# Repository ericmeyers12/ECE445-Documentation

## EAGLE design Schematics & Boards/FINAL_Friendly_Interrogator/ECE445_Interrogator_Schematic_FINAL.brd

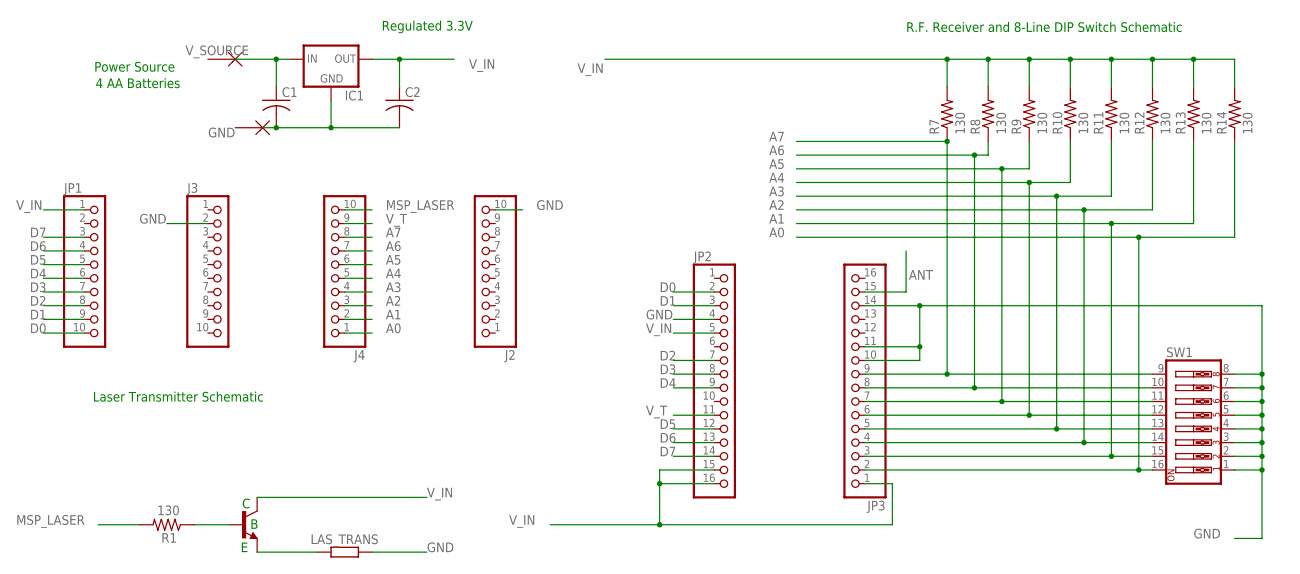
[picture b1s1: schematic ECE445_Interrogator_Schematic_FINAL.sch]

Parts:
C1, C2: C-US050-025X075; C050-025X075
IC1: 78LXX
J2, J3, J4: PINHD-1X10; 1X10
JP1: PINHD-1X10; 1X10
JP2, JP3: PINHD-1X16; 1X16
LAS_TRANS: R-EU_0204/5; 0204/5
Q2: BC338; TO92-EBC
R1, R7, R8, R9, R10, R11, R12, R13, R14: 130; 0204/5
SW1: SW_DIP-8; EDG-08
U$1, U$2: NO_CONNECT

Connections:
A0: J4.1, JP3.2, R14.1, SW1.16
A1: J4.2, JP3.3, R13.1, SW1.15
A2: J4.3, JP3.4, R12.1, SW1.14
A3: J4.4, JP3.5, R11.1, SW1.13
A4: J4.5, JP3.6, R10.1, SW1.12
A5: J4.6, JP3.7, R9.1, SW1.11
A6: J4.7, JP3.8, R8.1, SW1.10
A7: J4.8, JP3.9, R7.1, SW1.9
ANT: JP3.15
D0: JP1.10, JP2.2
D1: JP1.9, JP2.3
D2: JP1.8, JP2.7
D3: JP1.7, JP2.8
D4: JP1.6, JP2.9
D5: JP1.5, JP2.12
D6: JP1.4, JP2.13
D7: JP1.3, JP2.14
GND: C1.2, C2.2, IC1.GND, J2.10, J3.2, JP2.4, JP3.10, JP3.11, JP3.14, LAS_TRANS.2, SW1.1, SW1.2, SW1.3, SW1.4, SW1.5, SW1.6, SW1.7, SW1.8, U$1.P$1
MSP_LASER: J4.10, R1.2
unnamed: LAS_TRANS.1, Q2.E
unnamed: Q2.B, R1.1
V_IN: C2.1, IC1.OUT, JP1.1, JP2.5, JP2.15, JP2.16, JP3.1, Q2.C, R7.2, R8.2, R9.2, R10.2, R11.2, R12.2, R13.2, R14.2
V_SOURCE: C1.1, IC1.IN, U$2.P$1
V_T: J4.9, JP2.11

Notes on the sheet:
Power Source
4 AA Batteries
R.F. Receiver and 8-Line DIP Switch Schematic
Laser Transmitter Schematic
Regulated 3.3V

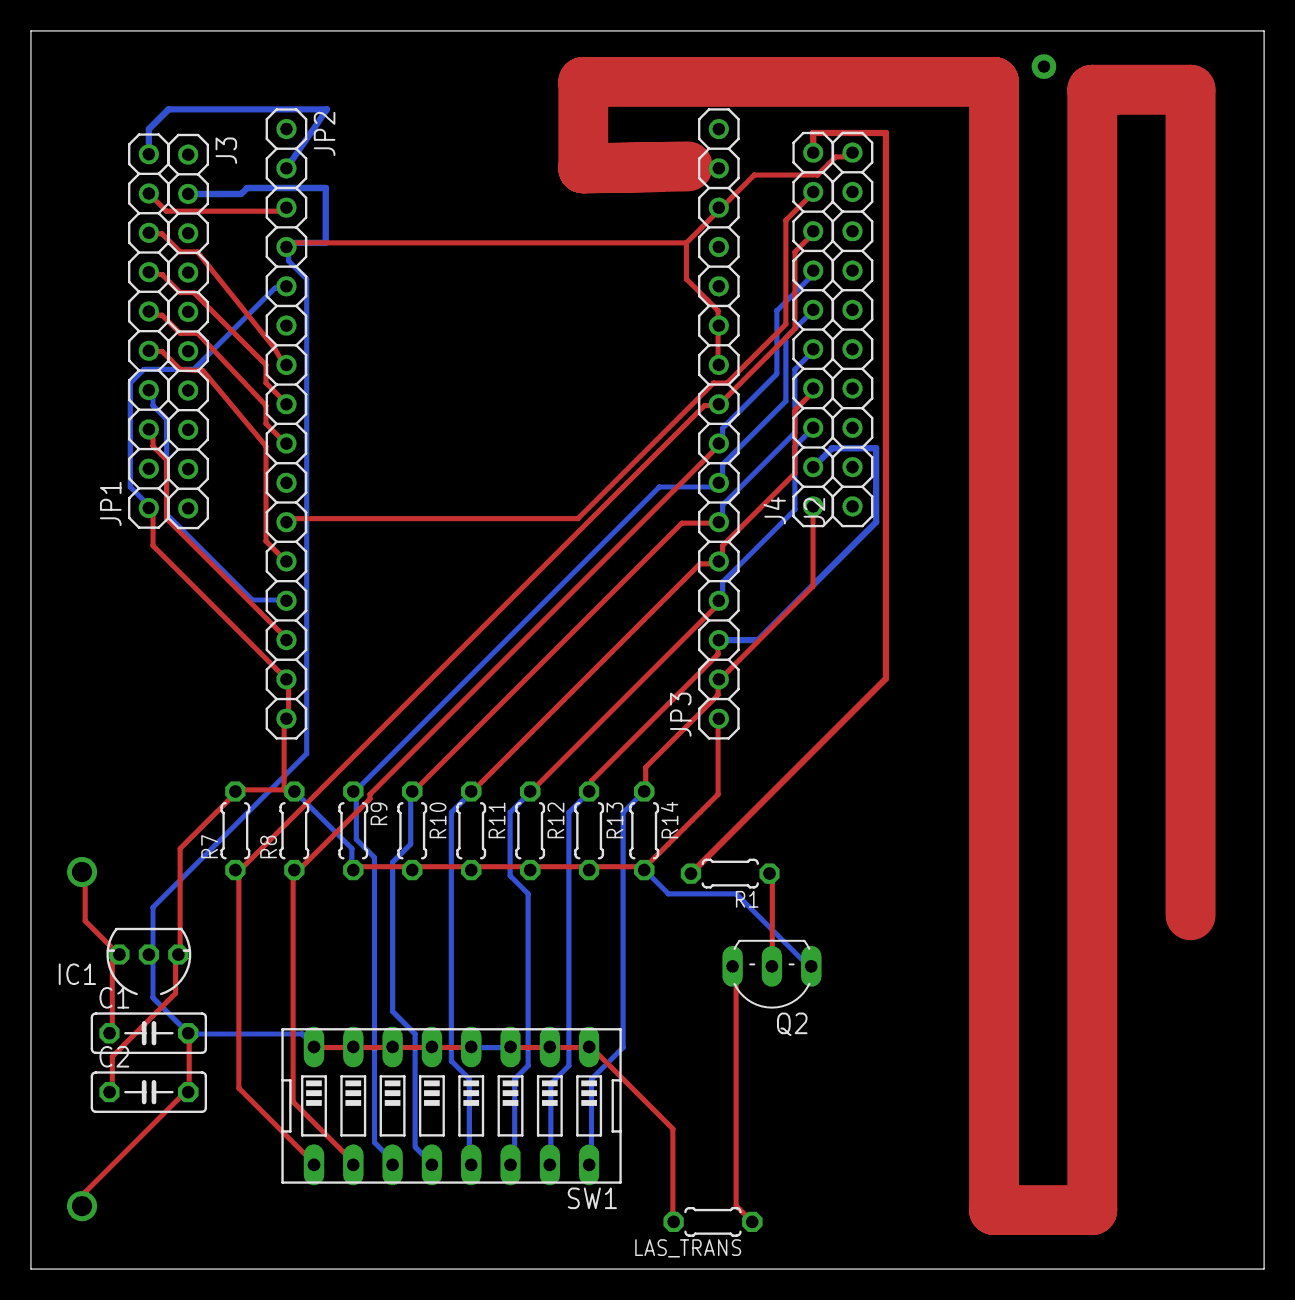
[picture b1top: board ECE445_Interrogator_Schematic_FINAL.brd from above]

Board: 2 copper layers, 79.7 x 80.0 mm, 23 parts (0 on the bottom side), 23 nets.

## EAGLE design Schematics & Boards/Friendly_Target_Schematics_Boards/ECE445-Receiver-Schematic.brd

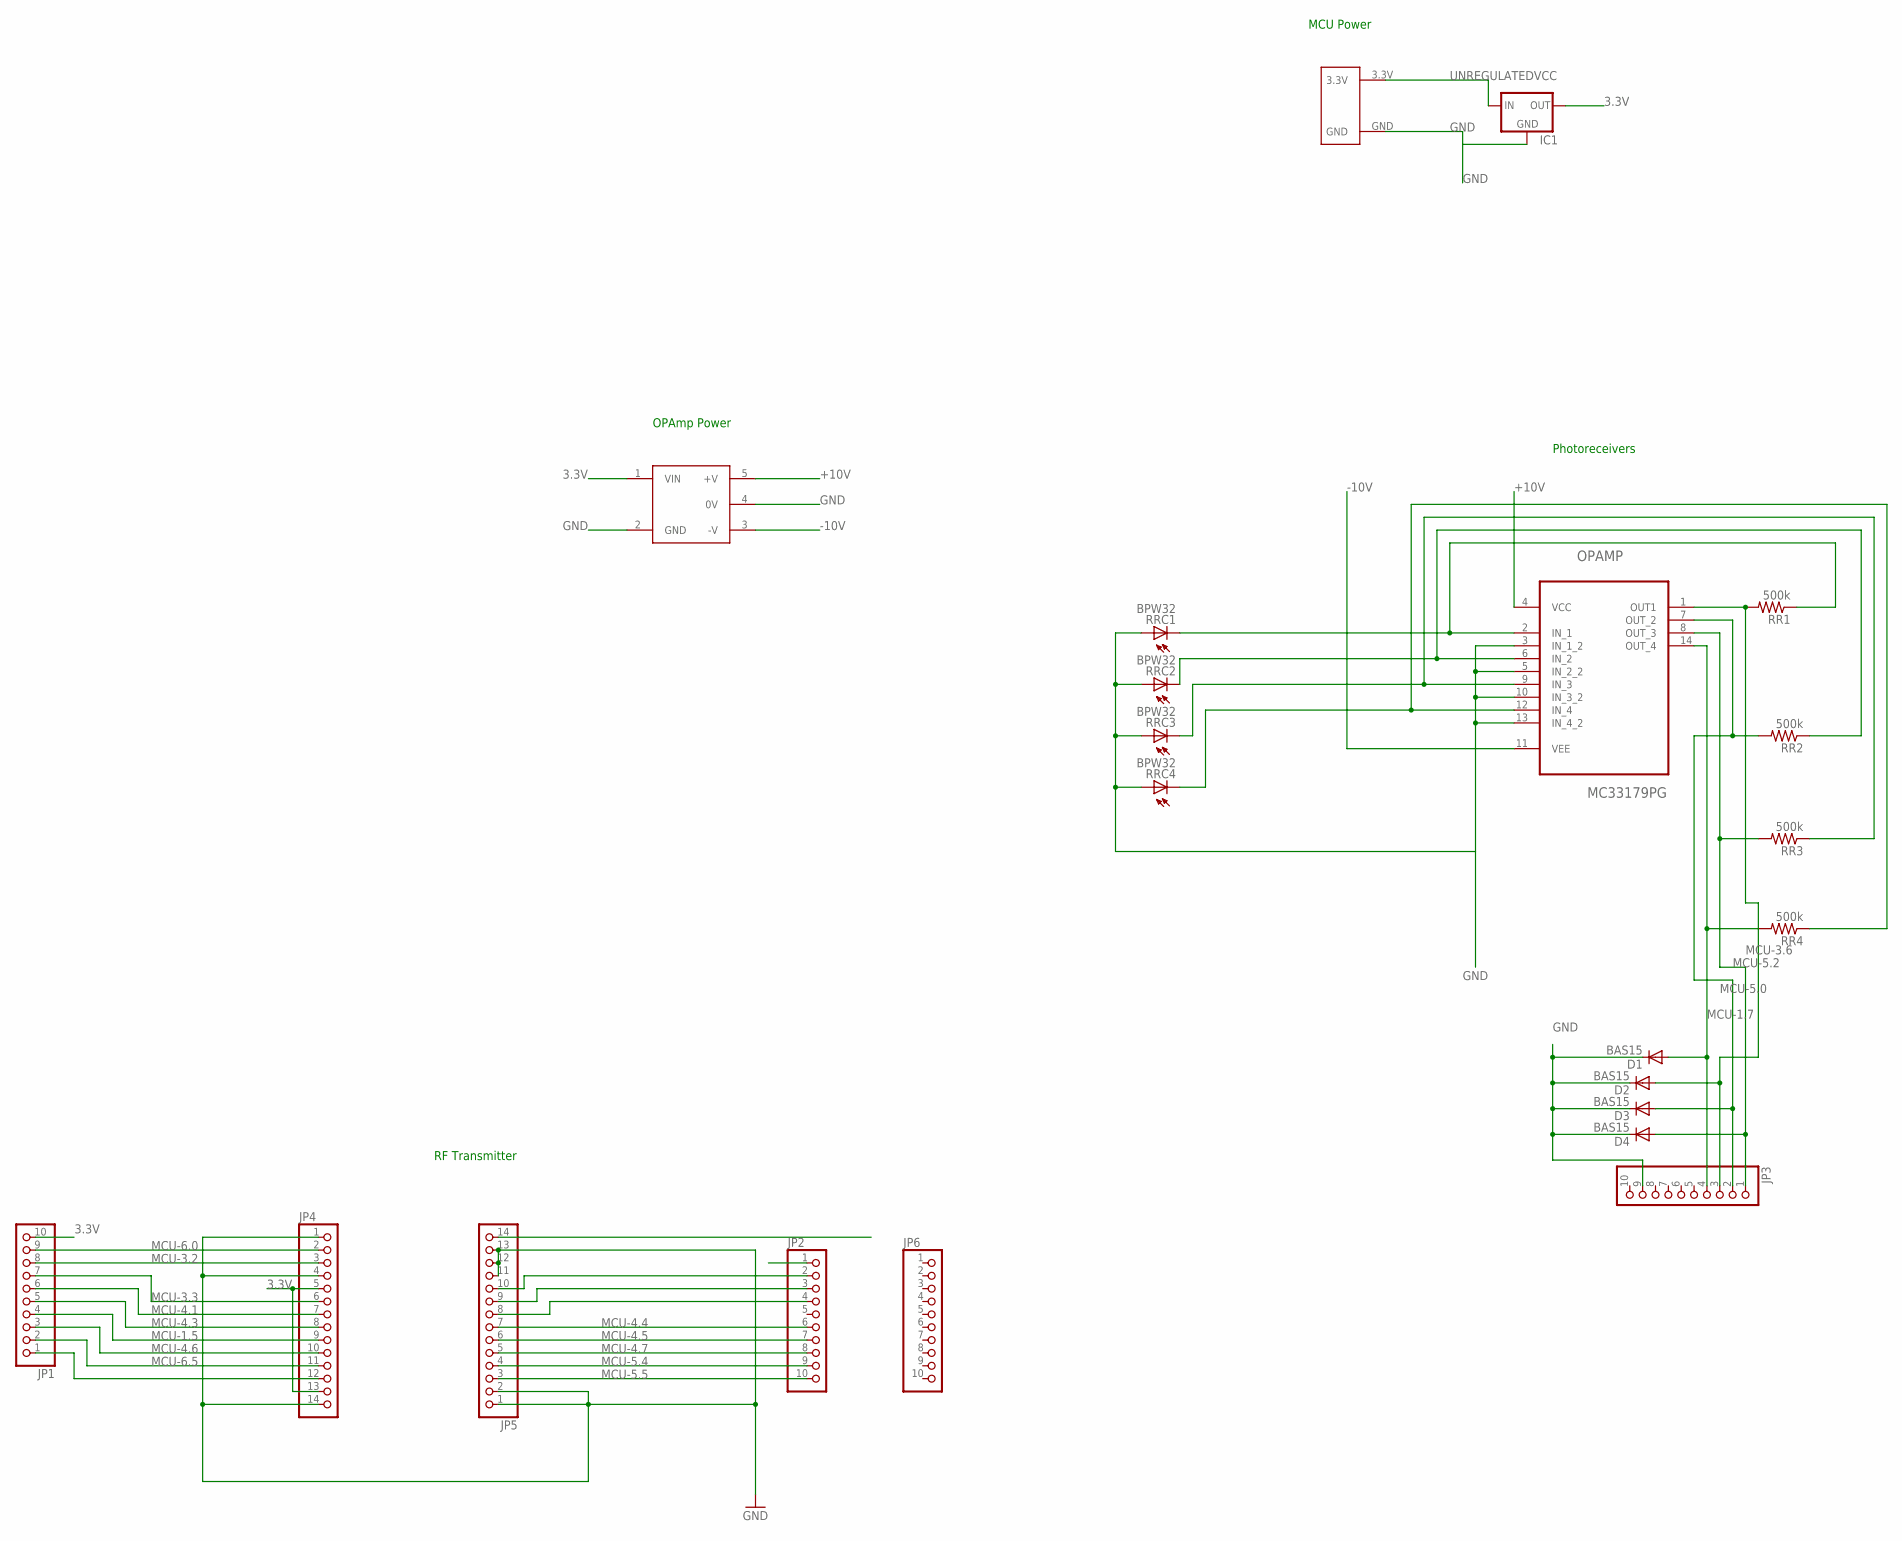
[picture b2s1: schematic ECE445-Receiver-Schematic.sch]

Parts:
D1, D2, D3, D4: BAS15; DO34-7
IC1: 78LXX
JP1, JP2, JP3, JP6: PINHD-1X10; 1X10
JP4, JP5: PINHD-1X14; 1X14
OPAMP: MC33179PG; DIP254P762X469-14
RR1, RR2, RR3, RR4: 500k; 0204/5
RRC1, RRC2, RRC3, RRC4: BPW32
U$13: PDM1-S3-D12-S
U$14: BATTERY

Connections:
3.3V: IC1.OUT, JP1.10, JP4.5, JP4.13, U$13.1 (VIN)
+10V: OPAMP.4 (VCC), U$13.5 (+V)
-10V: OPAMP.11 (VEE), U$13.3 (-V)
ANT: JP5.14
GND: D1.C, D2.C, D3.C, D4.C, IC1.GND, JP2.1, JP3.9, JP4.1, JP4.4, JP4.14, JP5.1, JP5.2, JP5.11, JP5.12, JP5.13, OPAMP.3 (IN_1_2), OPAMP.5 (IN_2_2), OPAMP.10 (IN_3_2), OPAMP.13 (IN_4_2), RRC1.A, RRC2.A, RRC3.A, RRC4.A, U$13.2 (GND), U$13.4 (0V), U$14.GND
MCU-1.5: JP1.4, JP4.9
MCU-1.7: D4.A, JP3.1, OPAMP.8 (OUT_3), RR3.2
MCU-3.2: JP1.8, JP4.3
MCU-3.3: JP1.7, JP4.6
MCU-3.6: D1.A, JP3.4, OPAMP.14 (OUT_4), RR4.2
MCU-4.1: JP1.6, JP4.7
MCU-4.3: JP1.5, JP4.8
MCU-4.4: JP2.6, JP5.7
MCU-4.5: JP2.7, JP5.6
MCU-4.6: JP1.3, JP4.10
MCU-4.7: JP2.8, JP5.5
MCU-5.0: D3.A, JP3.2, OPAMP.7 (OUT_2), RR2.2
MCU-5.2: D2.A, JP3.3, OPAMP.1 (OUT1), RR1.2
MCU-5.4: JP2.9, JP5.4
MCU-5.5: JP2.10, JP5.3
MCU-6.0: JP1.9, JP4.2
MCU-6.4: JP1.1, JP4.12
MCU-6.5: JP1.2, JP4.11
unnamed: JP2.2, JP5.10
unnamed: JP2.3, JP5.9
unnamed: JP2.4, JP5.8
unnamed: OPAMP.6 (IN_2), RR2.1, RRC2.K (C)
unnamed: OPAMP.9 (IN_3), RR3.1, RRC3.K (C)
RRC1: OPAMP.2 (IN_1), RR1.1, RRC1.K (C)
RRC4: OPAMP.12 (IN_4), RR4.1, RRC4.K (C)
UNREGULATEDVCC: IC1.IN, U$14.3.3V

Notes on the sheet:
RF Transmitter
Photoreceivers
MCU Power
OPAmp Power

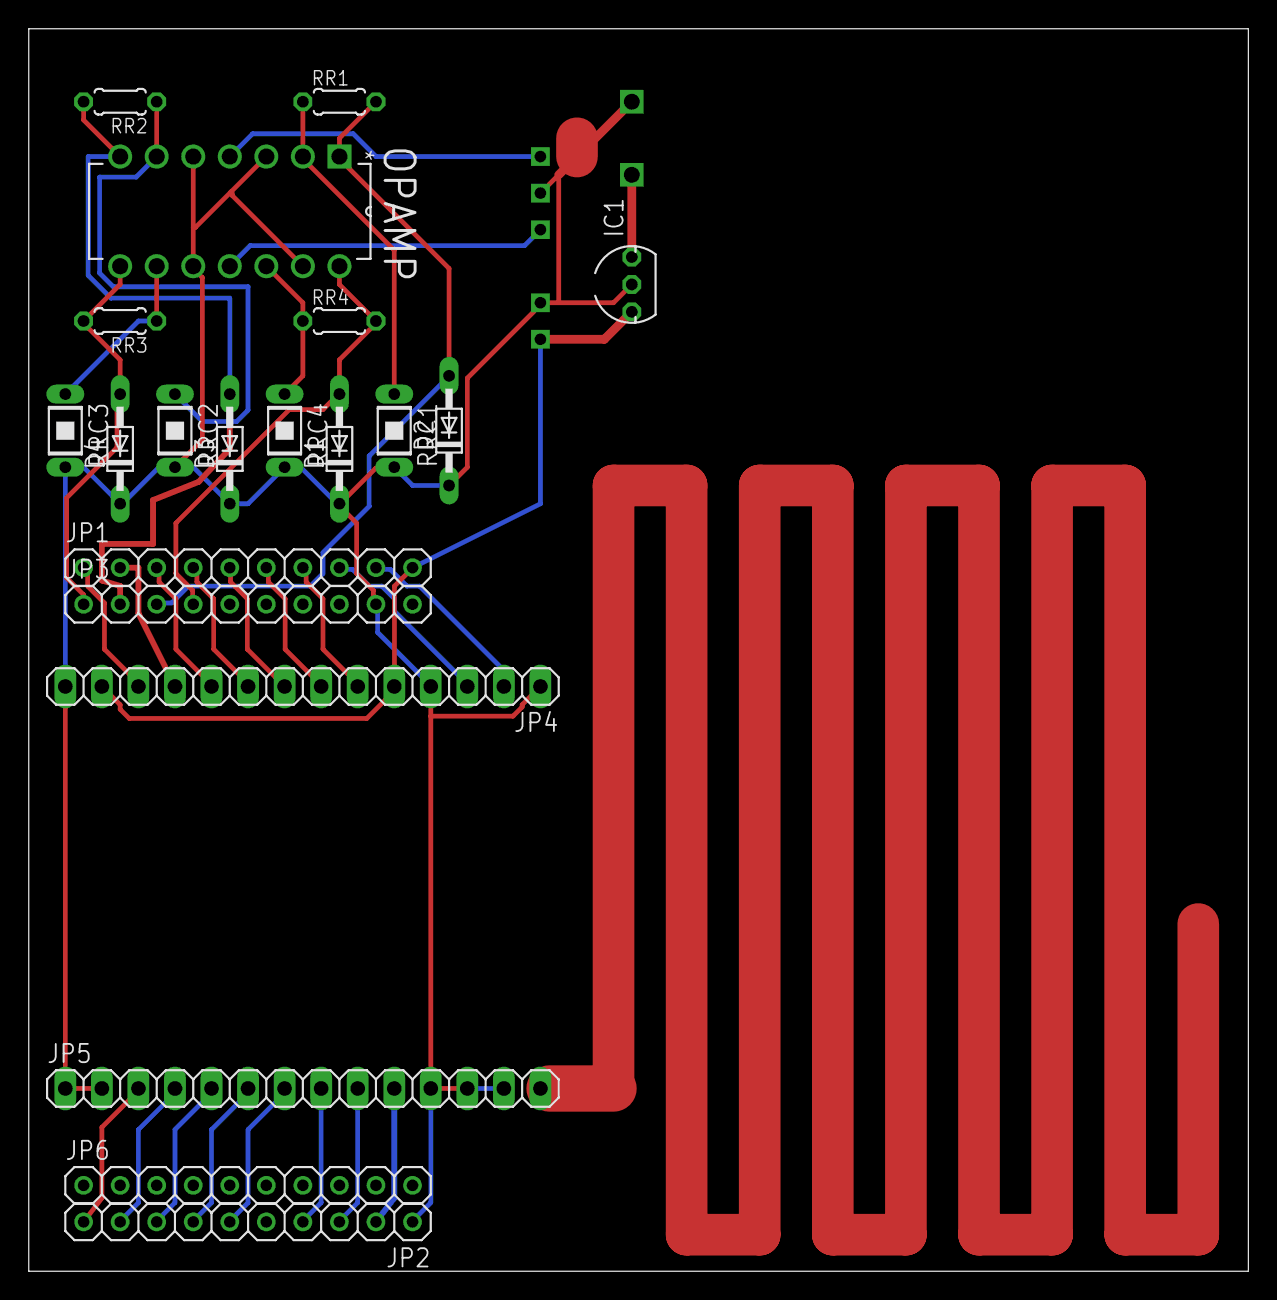
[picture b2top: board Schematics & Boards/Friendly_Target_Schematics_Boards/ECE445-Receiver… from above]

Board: 2 copper layers, 84.8 x 86.3 mm, 22 parts (0 on the bottom side), 30 nets.

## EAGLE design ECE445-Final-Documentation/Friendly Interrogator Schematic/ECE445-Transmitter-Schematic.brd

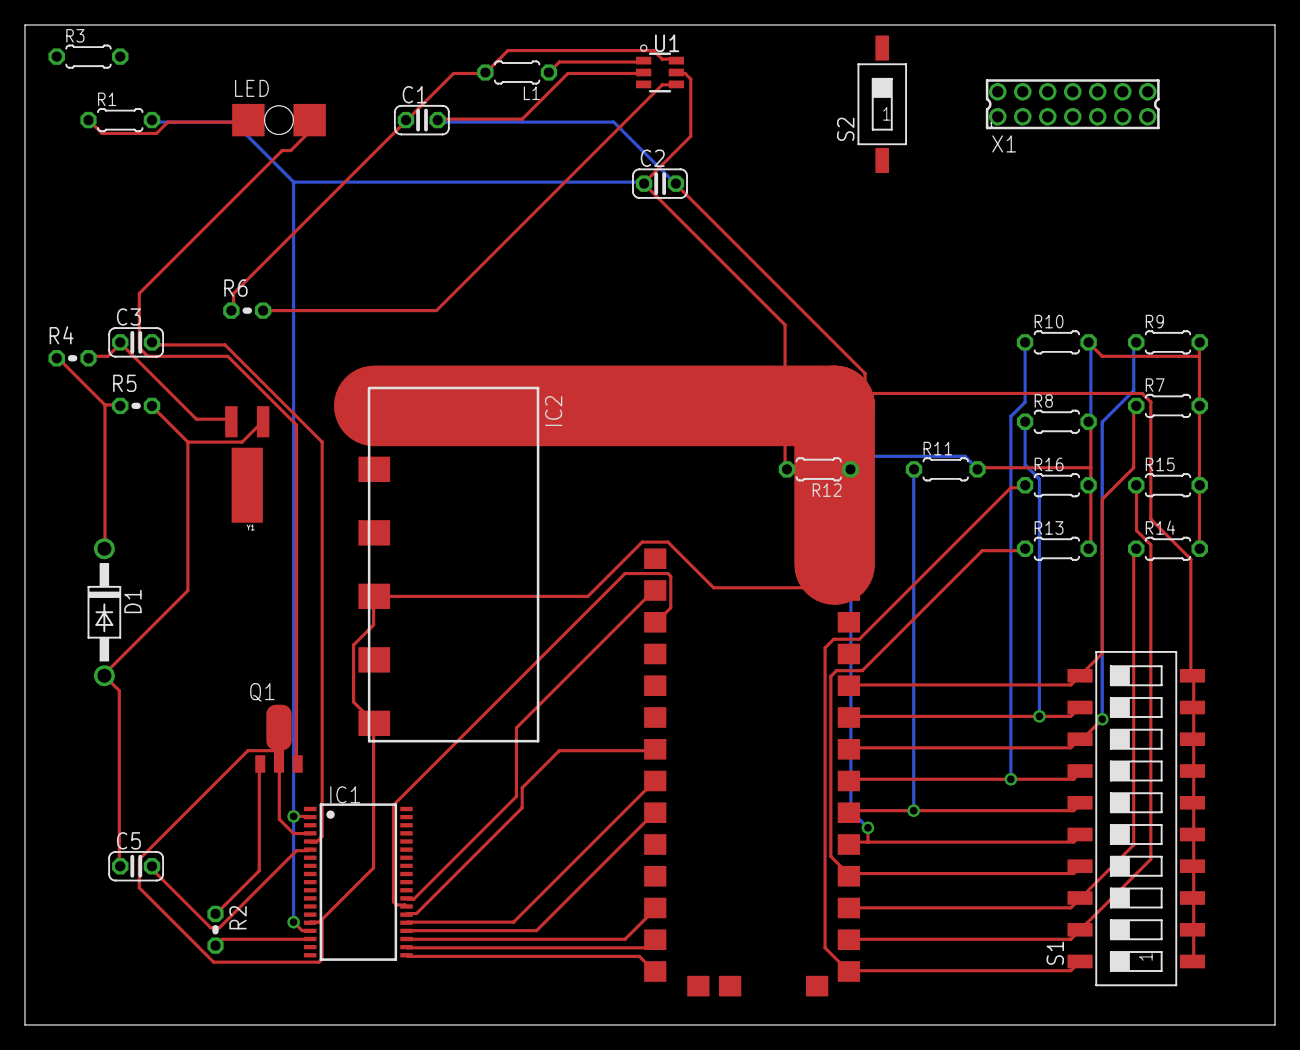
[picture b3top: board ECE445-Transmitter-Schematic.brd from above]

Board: 2 copper layers, 100.0 x 80.0 mm, 32 parts (0 on the bottom side), 33 nets.

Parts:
C1, C2: C025-024X044
C3, C5: 22 pF; C025-024X044
D1: DO41-10
IC1: MSP430F2274IDA; TSSOP38_R-PDSO-G38-DA
IC2: ANT-XXX-SP
L1: 0204/5
LED: P47F-BOTTOM
Q1: SOT89
R1, R3, R7, R8, R9, R10, R11, R12, R13, R14, R15, R16: 1.3 kohm; 0204/5
R2: 10 kohm; 0204V
R4: 33 kohm; 0204V
R5, R6: 100 Mohm; 0204V
S1: SWS010; SMS-010
S2: SWS001; SMS-001
U1: AAT1217ICA-3.3-T1; TSOT-23-6
U$1: KH3-RXM-LINX-315
X1: 87758-1416
Y1: CRYSTAL-32KHZ-SMD-MELF

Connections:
+3V3: C1.1, L1.2, R6.1, U1.6
GND: C1.2, C2.2, IC1.4, IC1.15, IC2.4, IC2.6, Q1.2, Q1.2@1, S1.1, S1.2, S1.3, S1.4, S1.5, S1.6, S1.7, S1.8, S1.9, S1.10, U1.2, U$1.27
unnamed: LED.C, Q1.3
unnamed: LED.A, R1.1
unnamed: IC1.17, R2.2
unnamed: C5.2, IC1.6
unnamed: C3.2, IC1.5
unnamed: C3.1, R4.2, Y1.X2
unnamed: Q1.1, R2.1
unnamed: D1.C, R4.1, R5.1
unnamed: IC2.1, U$1.28
unnamed: L1.1, U1.1
unnamed: C2.1, IC1.2, IC1.16, R1.2, R7.2, R8.2, R9.2, R10.2, R11.2, R12.2, R13.2, R14.2, R15.2, R16.2, U1.5
unnamed: C5.1, D1.A, R5.2, Y1.X1
unnamed: R15.1, S1.19, U$1.16
unnamed: R14.1, S1.18, U$1.17
unnamed: R13.1, S1.17, U$1.18
unnamed: R12.1, S1.16, U$1.19
unnamed: R6.2, U1.4
unnamed: R11.1, S1.15, U$1.20
unnamed: R10.1, S1.14, U$1.21
unnamed: IC1.20, U$1.14
unnamed: IC1.21, U$1.13
unnamed: IC1.22, U$1.12
unnamed: IC1.23, U$1.9
unnamed: IC1.24, U$1.8
unnamed: IC1.25, U$1.7
unnamed: IC1.26, U$1.3
unnamed: IC1.27, U$1.2
unnamed: R9.1, S1.13, U$1.22
unnamed: R8.1, S1.12, U$1.23
unnamed: R7.1, S1.11, U$1.24
unnamed: R16.1, S1.20, U$1.15

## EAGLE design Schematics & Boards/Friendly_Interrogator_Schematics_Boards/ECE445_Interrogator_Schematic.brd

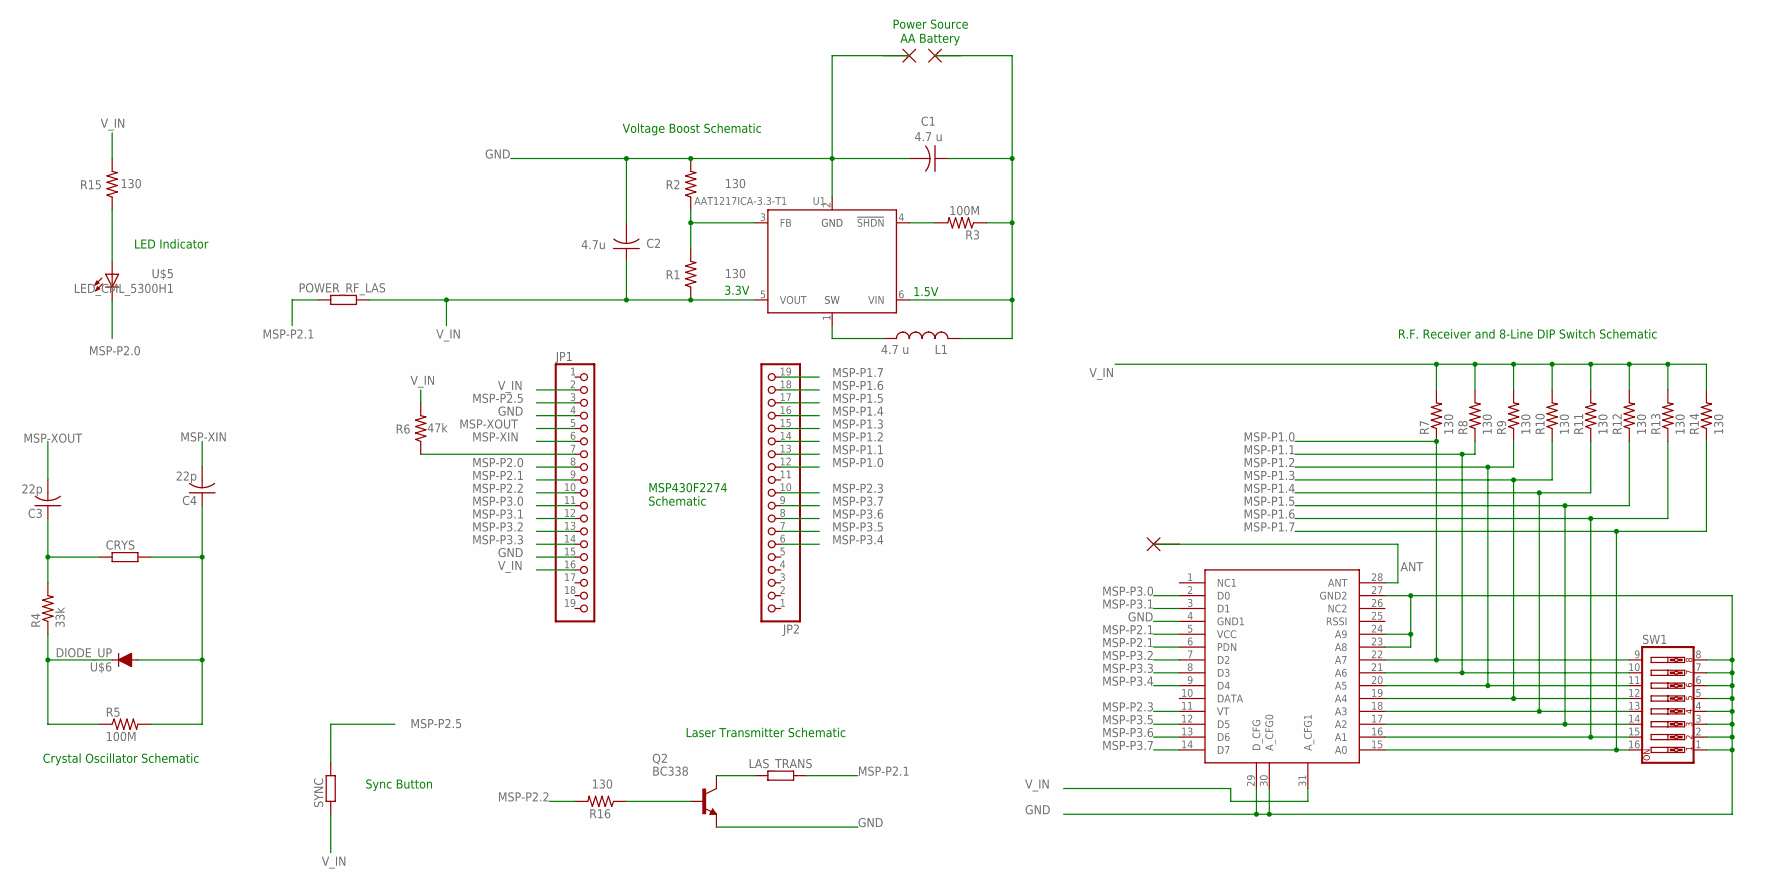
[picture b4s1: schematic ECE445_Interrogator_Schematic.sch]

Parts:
C1: 4.7 u; C025-024X044
C2: 4.7u; C025-024X044
C3, C4: 22p; C025-024X044
CRYS: R-EU_0204/5; 0204/5
JP1, JP2: PINHD-1X19; 1X19
L1: 4.7 u; 0204/5
LAS_TRANS: R-EU_0204/5; 0204/5
POWER_RF_LAS: R-EU_0204/5; 0204/5
Q2: BC338; TO92-EBC
R1, R2, R7, R8, R9, R10, R11, R12, R13, R14, R15, R16: 130; 0204/5
R3, R5: 100M; 0204V
R4: 33k; 0204V
R6: 47k; 0204/5
SW1: SW_DIP-8; EDG-08
SYNC: R-EU_0204/5; 0204/5
U1: AAT1217ICA-3.3-T1; TSOT-23-6
U$1: KH3-RXM-LINX-315
U$2, U$3, U$4: NO_CONNECT
U$5: LED_CML_5300H1
U$6: DIODE_UP; DIODEUP

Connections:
ANT: U$1.28 (ANT), U$4.P$1
GND: C1.2, C2.2, JP1.4, JP1.15, Q2.E, R2.2, SW1.1, SW1.2, SW1.3, SW1.4, SW1.5, SW1.6, SW1.7, SW1.8, U1.2 (GND), U$1.4 (GND1), U$1.23 (A8), U$1.24 (A9), U$1.27 (GND2), U$1.29 (D_CFG), U$1.30 (A_CFG0), U$2.P$1
MSP-P1.0: JP2.12, R7.1, SW1.9, U$1.22 (A7)
MSP-P1.1: JP2.13, R8.1, SW1.10, U$1.21 (A6)
MSP-P1.2: JP2.14, R9.1, SW1.11, U$1.20 (A5)
MSP-P1.3: JP2.15, R10.1, SW1.12, U$1.19 (A4)
MSP-P1.4: JP2.16, R11.1, SW1.13, U$1.18 (A3)
MSP-P1.5: JP2.17, R12.1, SW1.14, U$1.17 (A2)
MSP-P1.6: JP2.18, R13.1, SW1.15, U$1.16 (A1)
MSP-P1.7: JP2.19, R14.1, SW1.16, U$1.15 (A0)
MSP-P2.0: JP1.8, U$5.P$2 (C)
MSP-P2.1: JP1.9, LAS_TRANS.2, POWER_RF_LAS.1, U$1.5 (VCC), U$1.6 (PDN)
MSP-P2.2: JP1.10, R16.2
MSP-P2.3: JP2.10, U$1.11 (VT)
MSP-P2.5: JP1.3, SYNC.2
MSP-P3.0: JP1.11, U$1.2 (D0)
MSP-P3.1: JP1.12, U$1.3 (D1)
MSP-P3.2: JP1.13, U$1.7 (D2)
MSP-P3.3: JP1.14, U$1.8 (D3)
MSP-P3.4: JP2.6, U$1.9 (D4)
MSP-P3.5: JP2.7, U$1.12 (D5)
MSP-P3.6: JP2.8, U$1.13 (D6)
MSP-P3.7: JP2.9, U$1.14 (D7)
MSP-XIN: C4.2, JP1.6
MSP-XOUT: C3.2, JP1.5
unnamed: LAS_TRANS.1, Q2.C
unnamed: L1.1, U1.1 (SW)
unnamed: C1.1, L1.2, R3.1, U1.6 (VIN), U$3.P$1
unnamed: C3.1, CRYS.1, R4.2
unnamed: Q2.B, R16.1
unnamed: R4.1, R5.1, U$6.C
unnamed: R1.2, R2.1, U1.3 (FB)
unnamed: C4.1, CRYS.2, R5.2, U$6.A
unnamed: JP1.7, R6.1
unnamed: R3.2, U1.4 (!SHDN)
unnamed: R15.1, U$5.P$1 (A)
V_IN: C2.1, JP1.2, JP1.16, POWER_RF_LAS.2, R1.1, R6.2, R7.2, R8.2, R9.2, R10.2, R11.2, R12.2, R13.2, R14.2, R15.2, SYNC.1, U1.5 (VOUT), U$1.31 (A_CFG1)

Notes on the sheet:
MSP430F2274 Schematic
1.5V
3.3V
Voltage Boost Schematic
Power Source
AA Battery
R.F. Receiver and 8-Line DIP Switch Schematic
Crystal Oscillator Schematic
LED Indicator
Laser Transmitter Schematic
Sync Button

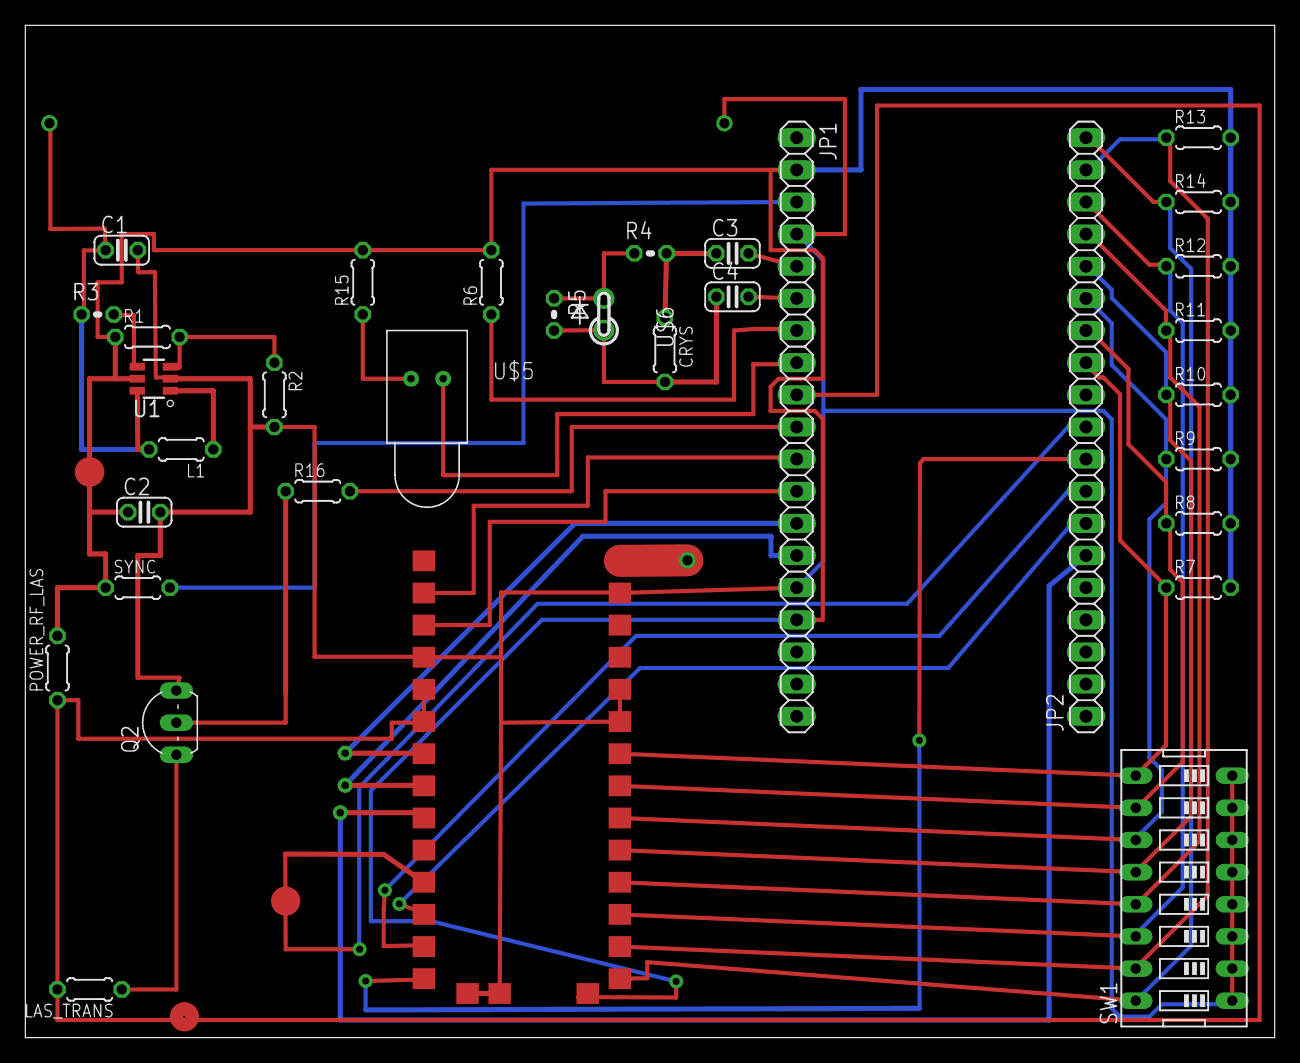
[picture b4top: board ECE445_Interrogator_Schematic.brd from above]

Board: 2 copper layers, 98.7 x 80.0 mm, 36 parts (0 on the bottom side), 37 nets.

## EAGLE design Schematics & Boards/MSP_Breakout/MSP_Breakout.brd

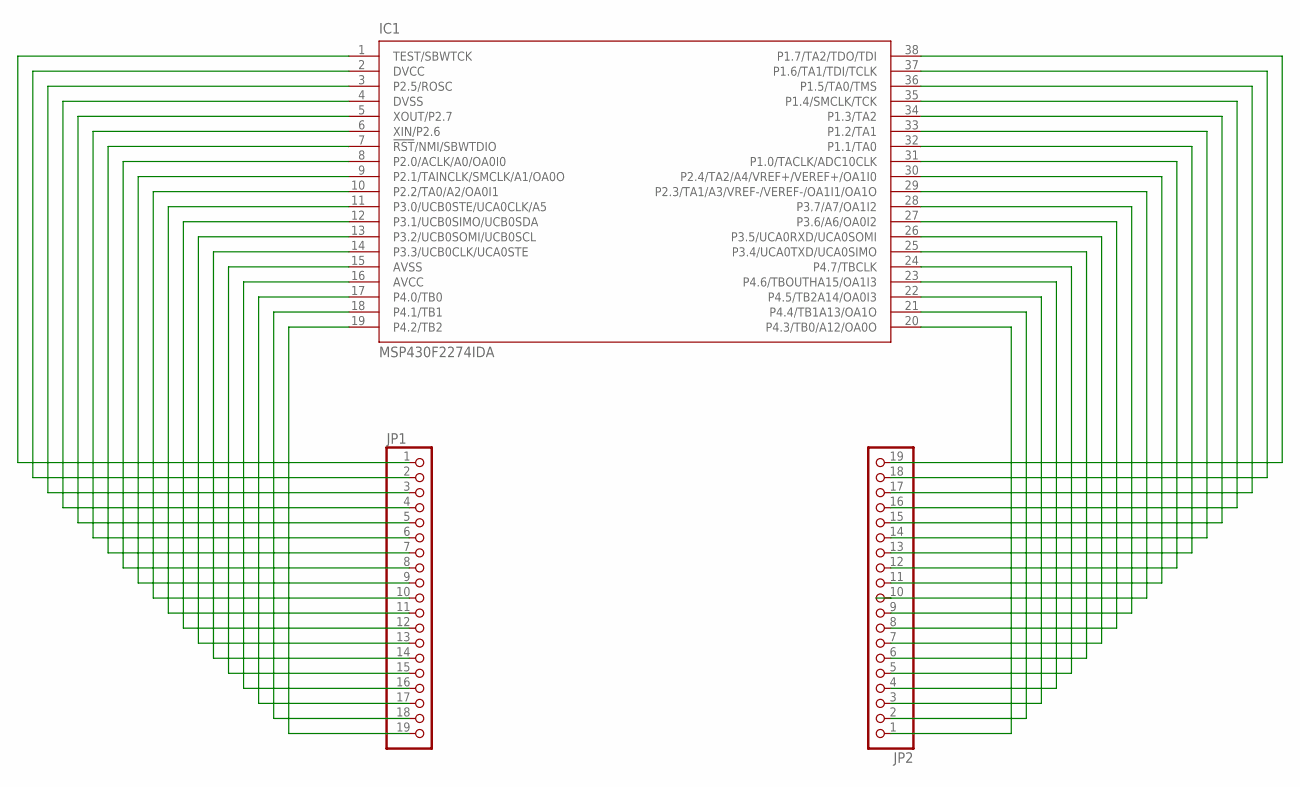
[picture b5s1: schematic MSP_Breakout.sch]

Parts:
IC1: MSP430F2274IDA; TSSOP38_R-PDSO-G38-DA
JP1, JP2: PINHD-1X19; 1X19

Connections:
unnamed: IC1.1 (TEST/SBWTCK), JP1.1
unnamed: IC1.2 (DVCC), JP1.2
unnamed: IC1.3 (P2.5/ROSC), JP1.3
unnamed: IC1.4 (DVSS), JP1.4
unnamed: IC1.5 (XOUT/P2.7), JP1.5
unnamed: IC1.6 (XIN/P2.6), JP1.6
unnamed: IC1.7 (!RST!/NMI/SBWTDIO), JP1.7
unnamed: IC1.8 (P2.0/ACLK/A0/OA0I0), JP1.8
unnamed: IC1.9 (P2.1/TAINCLK/SMCLK/A1/OA0O), JP1.9
unnamed: IC1.10 (P2.2/TA0/A2/OA0I1), JP1.10
unnamed: IC1.11 (P3.0/UCB0STE/UCA0CLK/A5), JP1.11
unnamed: IC1.12 (P3.1/UCB0SIMO/UCB0SDA), JP1.12
unnamed: IC1.13 (P3.2/UCB0SOMI/UCB0SCL), JP1.13
unnamed: IC1.14 (P3.3/UCB0CLK/UCA0STE), JP1.14
unnamed: IC1.15 (AVSS), JP1.15
unnamed: IC1.16 (AVCC), JP1.16
unnamed: IC1.17 (P4.0/TB0), JP1.17
unnamed: IC1.18 (P4.1/TB1), JP1.18
unnamed: IC1.19 (P4.2/TB2), JP1.19
unnamed: IC1.38 (P1.7/TA2/TDO/TDI), JP2.19
unnamed: IC1.37 (P1.6/TA1/TDI/TCLK), JP2.18
unnamed: IC1.36 (P1.5/TA0/TMS), JP2.17
unnamed: IC1.35 (P1.4/SMCLK/TCK), JP2.16
unnamed: IC1.34 (P1.3/TA2), JP2.15
unnamed: IC1.33 (P1.2/TA1), JP2.14
unnamed: IC1.32 (P1.1/TA0), JP2.13
unnamed: IC1.31 (P1.0/TACLK/ADC10CLK), JP2.12
unnamed: IC1.30 (P2.4/TA2/A4/VREF+/VEREF+/OA1I0), JP2.11
unnamed: IC1.29 (P2.3/TA1/A3/VREF-/VEREF-/OA1I1/OA1O), JP2.10
unnamed: IC1.28 (P3.7/A7/OA1I2), JP2.9
unnamed: IC1.27 (P3.6/A6/OA0I2), JP2.8
unnamed: IC1.26 (P3.5/UCA0RXD/UCA0SOMI), JP2.7
unnamed: IC1.25 (P3.4/UCA0TXD/UCA0SIMO), JP2.6
unnamed: IC1.24 (P4.7/TBCLK), JP2.5
unnamed: IC1.23 (P4.6/TBOUTHA15/OA1I3), JP2.4
unnamed: IC1.22 (P4.5/TB2A14/OA0I3), JP2.3
unnamed: IC1.21 (P4.4/TB1A13/OA1O), JP2.2
unnamed: IC1.20 (P4.3/TB0/A12/OA0O), JP2.1

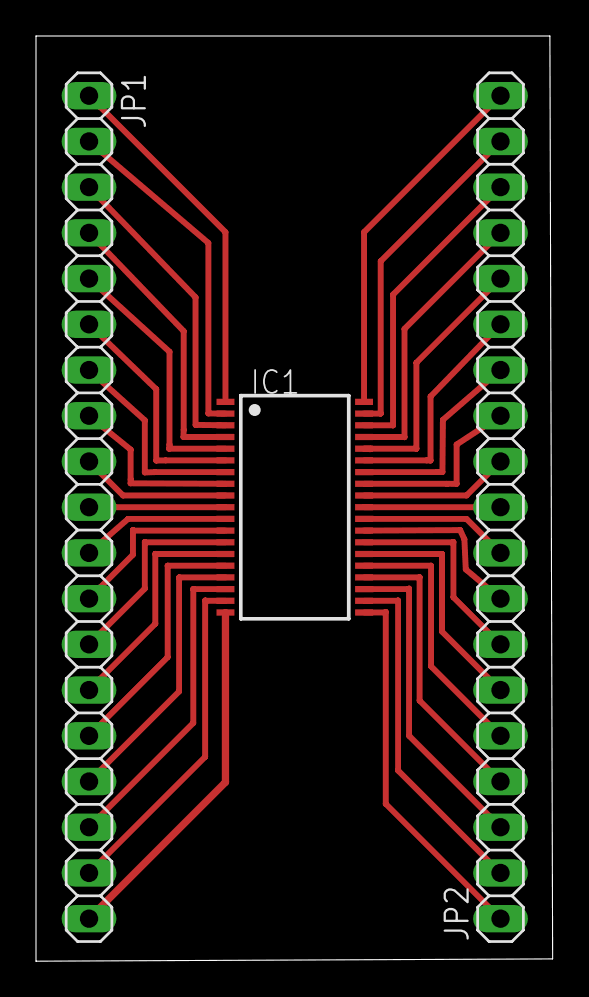
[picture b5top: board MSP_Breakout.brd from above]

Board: 2 copper layers, 28.7 x 51.4 mm, 3 parts (0 on the bottom side), 38 nets.

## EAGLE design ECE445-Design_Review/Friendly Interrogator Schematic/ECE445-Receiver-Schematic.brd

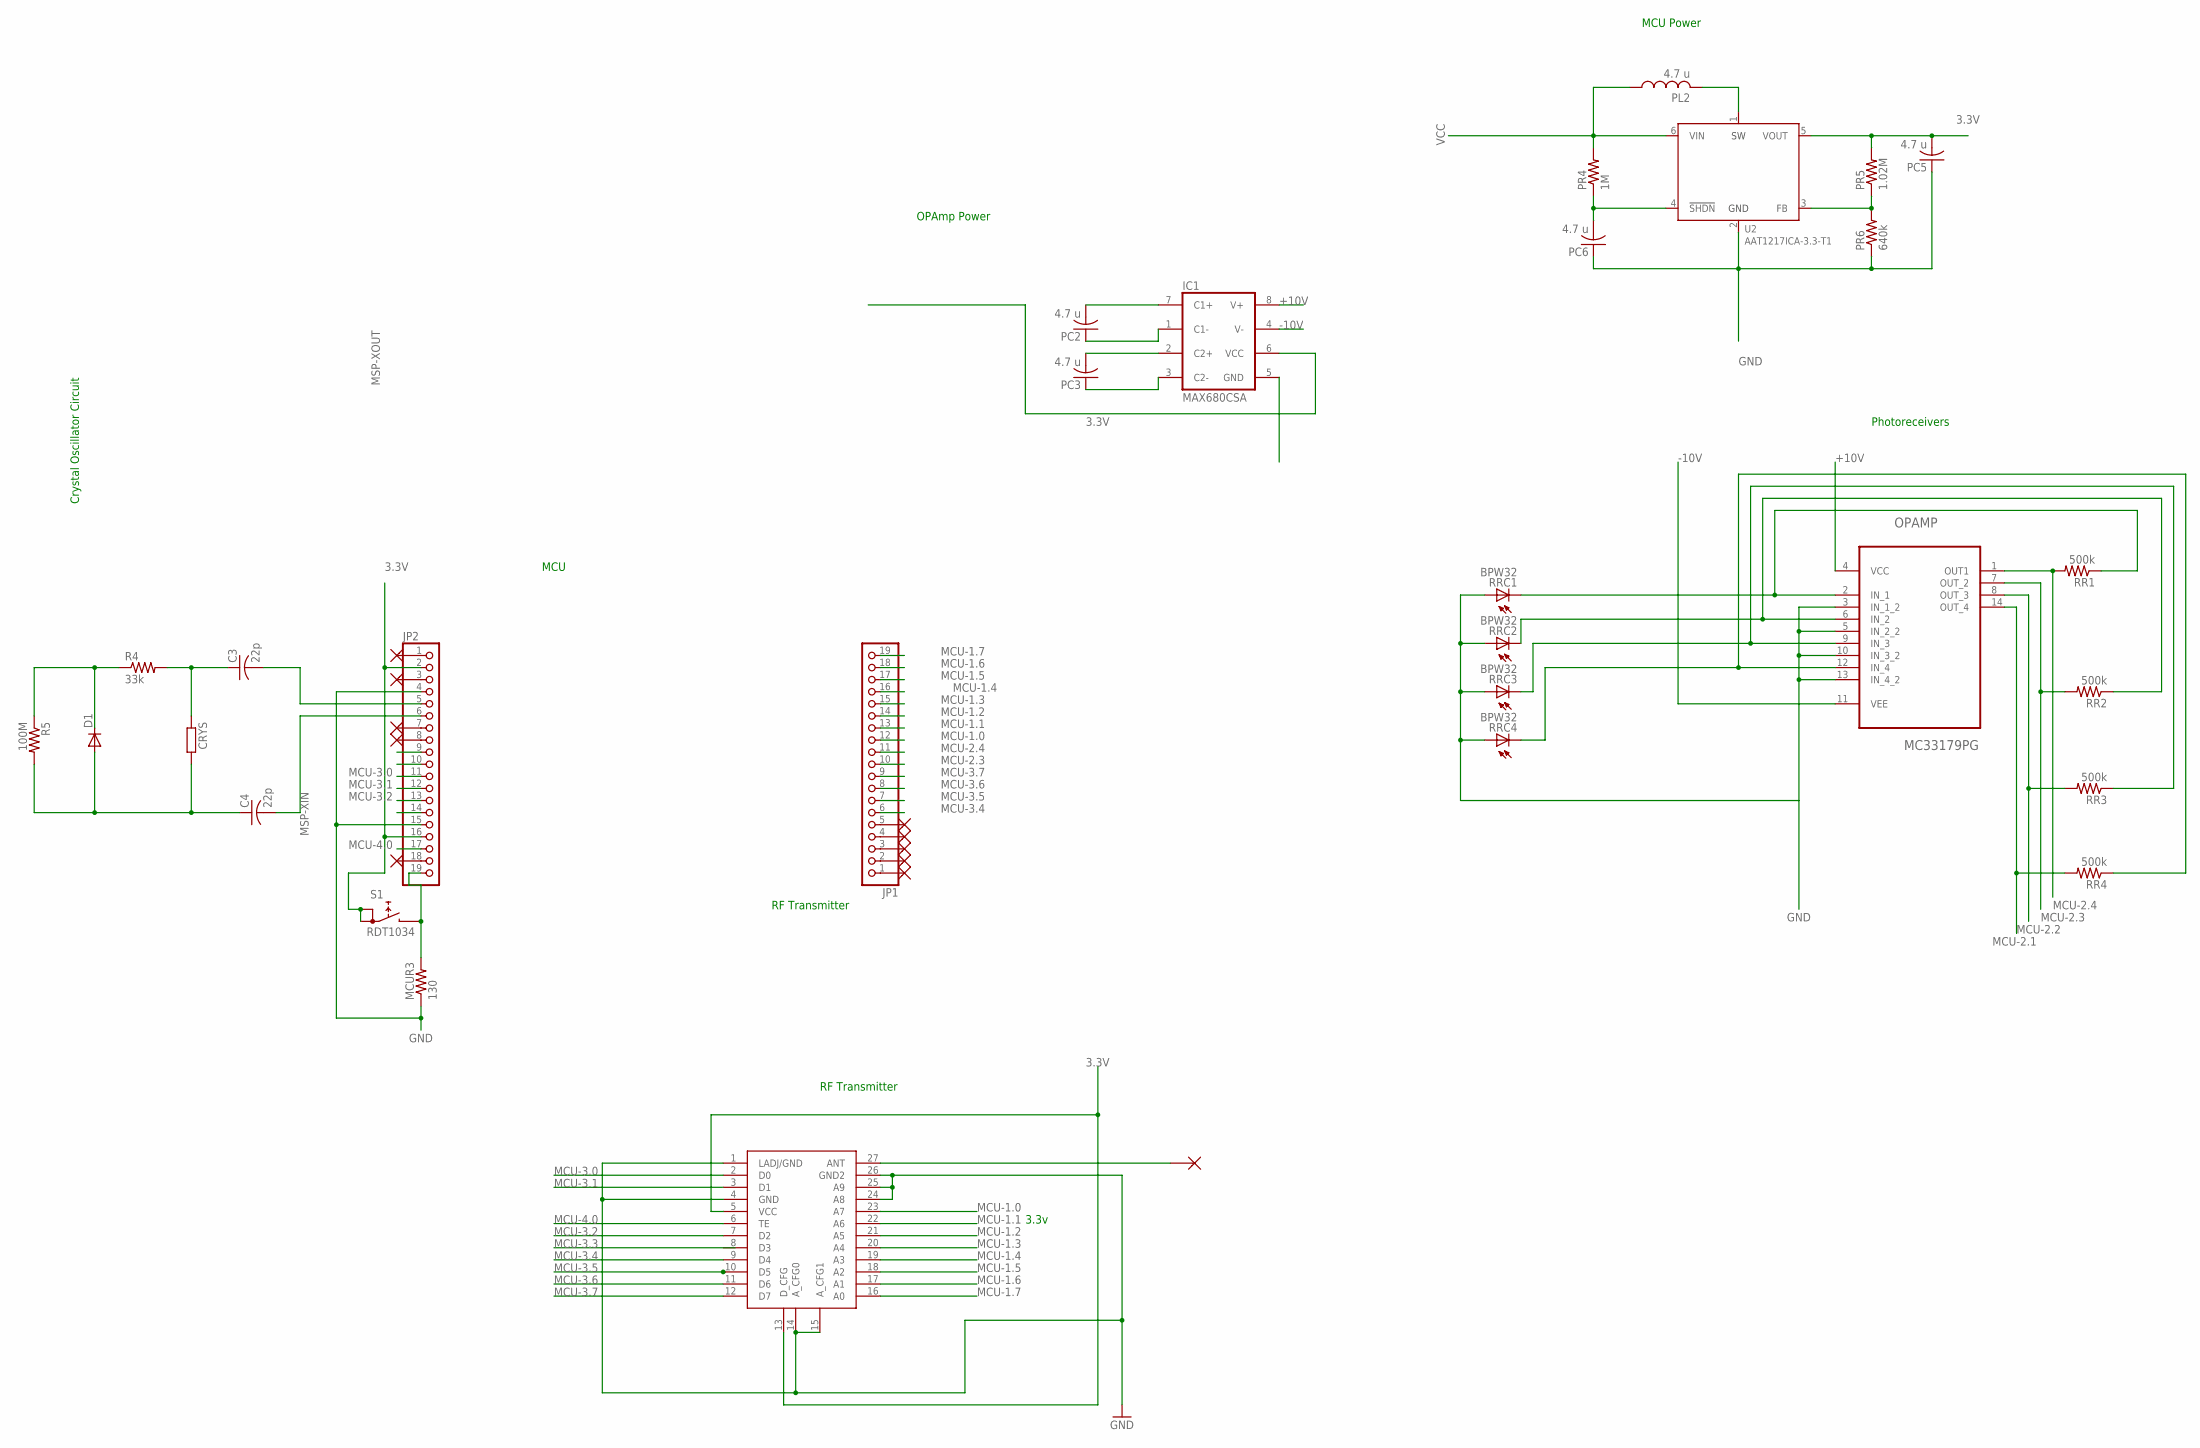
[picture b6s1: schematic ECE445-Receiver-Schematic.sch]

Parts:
C3, C4: 22p; C025-024X044
CRYS: R-EU_0204/5; 0204/5
D1: 1N4004; DO41-10
IC1: MAX680CSA; SO08
JP1, JP2: PINHD-1X19; 1X19
MCUR3: 130; 0204/5
OPAMP: MC33179PG; DIP254P762X469-14
PC2, PC3, PC5, PC6: 4.7 u; C025-024X044
PL2: 4.7 u; 0204/5
PR4: 1M; 0204/5
PR5: 1.02M; 0204/5
PR6: 640k; 0204/5
R4: 33k; 0204V
R5: 100M; 0204V
RR1, RR2, RR3, RR4: 500k; 0204/5
RRC1, RRC2, RRC3, RRC4: BPW32
S1: RDT1034
U2: AAT1217ICA-3.3-T1; TSOT-23-6
U$1: LINX-KH3-TRANSMITTER
U$2, U$3, U$4, U$5, U$6, U$7, U$8, U$9, U$10, U$11, U$12: NO_CONNECT

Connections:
3.3V: IC1.6 (VCC), JP2.2, JP2.16, PC5.2, PR5.2, S1.A, S1.A1, U2.5 (VOUT), U$1.5 (VCC), U$1.13 (D_CFG); also elsewhere on the board
+10V: IC1.8 (V+), OPAMP.4 (VCC); also elsewhere on the board
-10V: IC1.4 (V-), OPAMP.11 (VEE); also elsewhere on the board
GND: IC1.5 (GND), JP2.4, JP2.15, MCUR3.1, OPAMP.3 (IN_1_2), OPAMP.5 (IN_2_2), OPAMP.10 (IN_3_2), OPAMP.13 (IN_4_2), PC5.1, PC6.1, PR6.1, RRC1.A, RRC2.A, RRC3.A, RRC4.A, U2.2 (GND), U$1.1 (LADJ/GND), U$1.4 (GND), U$1.14 (A_CFG0), U$1.15 (A_CFG1), U$1.24 (A8), U$1.25 (A9), U$1.26 (GND2); also elsewhere on the board
MCU-1.0: JP1.12, U$1.23 (A7)
MCU-1.1: JP1.13, U$1.22 (A6)
MCU-1.2: JP1.14, U$1.21 (A5)
MCU-1.3: JP1.15, U$1.20 (A4)
MCU-1.4: JP1.16, U$1.19 (A3)
MCU-1.5: JP1.17, U$1.18 (A2)
MCU-1.6: JP1.18, U$1.17 (A1)
MCU-1.7: JP1.19, U$1.16 (A0)
MCU-2.1: JP2.9, OPAMP.14 (OUT_4), RR4.2
MCU-2.2: JP2.10, OPAMP.8 (OUT_3), RR3.2
MCU-2.3: JP1.10, OPAMP.7 (OUT_2), RR2.2
MCU-2.4: JP1.11, OPAMP.1 (OUT1), RR1.2
MCU-3.0: JP2.11, U$1.2 (D0)
MCU-3.1: JP2.12, U$1.3 (D1)
MCU-3.2: JP2.13, U$1.7 (D2)
MCU-3.3: JP2.14
MCU-3.4: JP1.6, U$1.9 (D4)
MCU-3.5: JP1.7, U$1.10 (D5)
MCU-3.6: JP1.8, U$1.11 (D6)
MCU-3.7: JP1.9, U$1.12 (D7)
MCU-4.0: JP2.17, U$1.6 (TE)
MSP-XIN: C4.2, JP2.6
MSP-XOUT: C3.2, JP2.5
unnamed: PC6.2, PR4.1, U2.4 (!SHDN)
unnamed: JP2.19, MCUR3.2, S1.B
unnamed: C3.1, CRYS.1, R4.2
unnamed: D1.C, R4.1, R5.1
unnamed: OPAMP.6 (IN_2), RR2.1, RRC2.K (C)
unnamed: C4.1, CRYS.2, D1.A, R5.2
unnamed: OPAMP.9 (IN_3), RR3.1, RRC3.K (C)
unnamed: IC1.1 (C1-), PC2.1
unnamed: IC1.2 (C2+), PC3.2
unnamed: IC1.3 (C2-), PC3.1
unnamed: IC1.7 (C1+), PC2.2
POWERL2: PL2.2, U2.1 (SW)
POWERR1: PR5.1, PR6.2, U2.3 (FB)
RRC1: OPAMP.2 (IN_1), RR1.1, RRC1.K (C)
RRC4: OPAMP.12 (IN_4), RR4.1, RRC4.K (C)
VCC: PL2.1, PR4.2, U2.6 (VIN)

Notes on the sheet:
RF Transmitter
3.3v
Photoreceivers
MCU Power
OPAmp Power
MCU
Crystal Oscillator Circuit

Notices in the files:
parts and their libraries:
SparkFun-FreqCtrl: Licensing: Creative Commons ShareAlike 4.0 International - https://creativecommons.org/licenses/by-sa/4.0
